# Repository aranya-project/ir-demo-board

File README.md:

# IR Demo FeatherWing

This is a carrier board for an Adafruit Feather device, designed specifically
for the ESP32-S3 Feather. It breaks out two UARTs into IR transceivers, and SPI
to a microSD slot.

## Board View

## Assembly Options

There are three sets of components for the IR transceivers, but only two
can be used. The sections marked IR1 are shared, connected to UART1, and
only one section needs to be populated. The section marked IR2 is
connected to UART2.

Technically, the only components that have to be installed are one
transceiver and two links to power them (across R1/R3 on the top, R2/R4
on the left, and R6/R13 on the right). The capacitors improve stability
but aren't strictly required. The other resistors are pull-ups for the
SD lines (recommended but makes little practical difference) and
pull-ups for the IR shutdown (only really necessary if you plan on
shutting down the CPU)

## IR Transceivers

IR1 is connected to UART1 on the standard Feather TX/RX pins, which are
on GPIOs 39 and 38, respectively. IR2 is connected to UART2 on GPIOs 5
and 6. Each transceiver has an active low enable pin that is by default
pulled high. These are on GPIOs 8 and 9 for IR1 and IR2.

Enabling IrDA mode requires setting `UART_IRDA_EN` in `UART_CONF0_REG`.
Additionally, to transmit, you need to set `UART_IRDA_TX_EN`. By
default, IrDA mode is half duplex, and `UART_IRDA_TX_EN` needs to be
toggled to switch between transmit and receive modes. To enable both
transmit and receive at the same time, which will echo all transmitted
data through the RX line, set `UART_IRDA_DPLX`.

For reasons I don't understand, the only thing that can be set via IDF
APIs is enabling IrDA mode. All of the other IrDA settings are not
available via IDF APIs, so you will likely have to twiddle the registers
directly. In C, this can be done by including `soc/uart_struct.h` and
using the bitfield structs provided. i.e.

```
UART1.conf0.irda_dplx = 1;
```

### Pin Summary (IR1 on UART1)

| GPIO Pin | Function |
|----------|----------|
| 39 | Transmit |
| 38 | Receive |
| 8 | Enable (active low) |

### Pin Summary (IR2 on UART2)

| GPIO Pin | Function |
|----------|----------|
| 5 | Transmit |
| 6 | Receive |
| 9 | Enable (active low) |

## Micro SD

The SD card is connected to SPI such that it should be usable directly
through the IOMUX on IOs 35, 36, and 37. CS is connected to GPIO 11.
Card detect is connected to GPIO 13.

Additionally, DAT1 and DAT2 (only used in SD mode) are connected to
GPIOs 12 and 10, respectively, so you should theoretically be able to
enable 4-bit SD through the SD/MMC controller.

### Pin Summary (SPI mode)

| GPIO Pin | Function |
|----------|----------|
| 36 | SCK |
| 35 | MOSI |
| 37 | MISO |
| 11 | CS |

### Pin Summary (SD 1-bit mode)

| GPIO Pin | Function |
|----------|----------|
| 36 | CLK |
| 35 | CMD |
| 37 | DAT0 |
| 11 | CD |

### Pin Summary (SD 4-bit mode)

| GPIO Pin | Function |
|----------|----------|
| 36 | CLK |
| 35 | CMD |
| 37 | DAT0 |
| 12 | DAT1 |
| 10 | DAT2 |
| 11 | DAT3 |

## Headers

 GPIOs 14-18 are unused and are broken out for futher expansion. The I2C
 lines are also available, as well as VBATT, VBUS, 3V3, GND, EN, and
 ~RST.

## Mechanical

The board is 1.4 inches wide and 2.3 inches tall (35.56 x 58.42mm). The
component sizes should be similar to their footprint outlines, giving it
a maximum horizontal extent of 1.51" (38.354mm) with both side IR
transceivers installed, and a maximum vertical extent of 2.51"
(63.754mm) with the top transceiver installed and an SD card inserted.

Four mounting holes on the corners are sized for M2.5 screws. They are
0.11" (2.794mm) from the edges, which is also the corner radius.

A 0.15x0.25 inch (3.81x6.35mm) cutout is provided near the Feather's
battery connector in the upper right. This allows any battery cables to
be routed below the board even if the board is mounted flush against a
case.

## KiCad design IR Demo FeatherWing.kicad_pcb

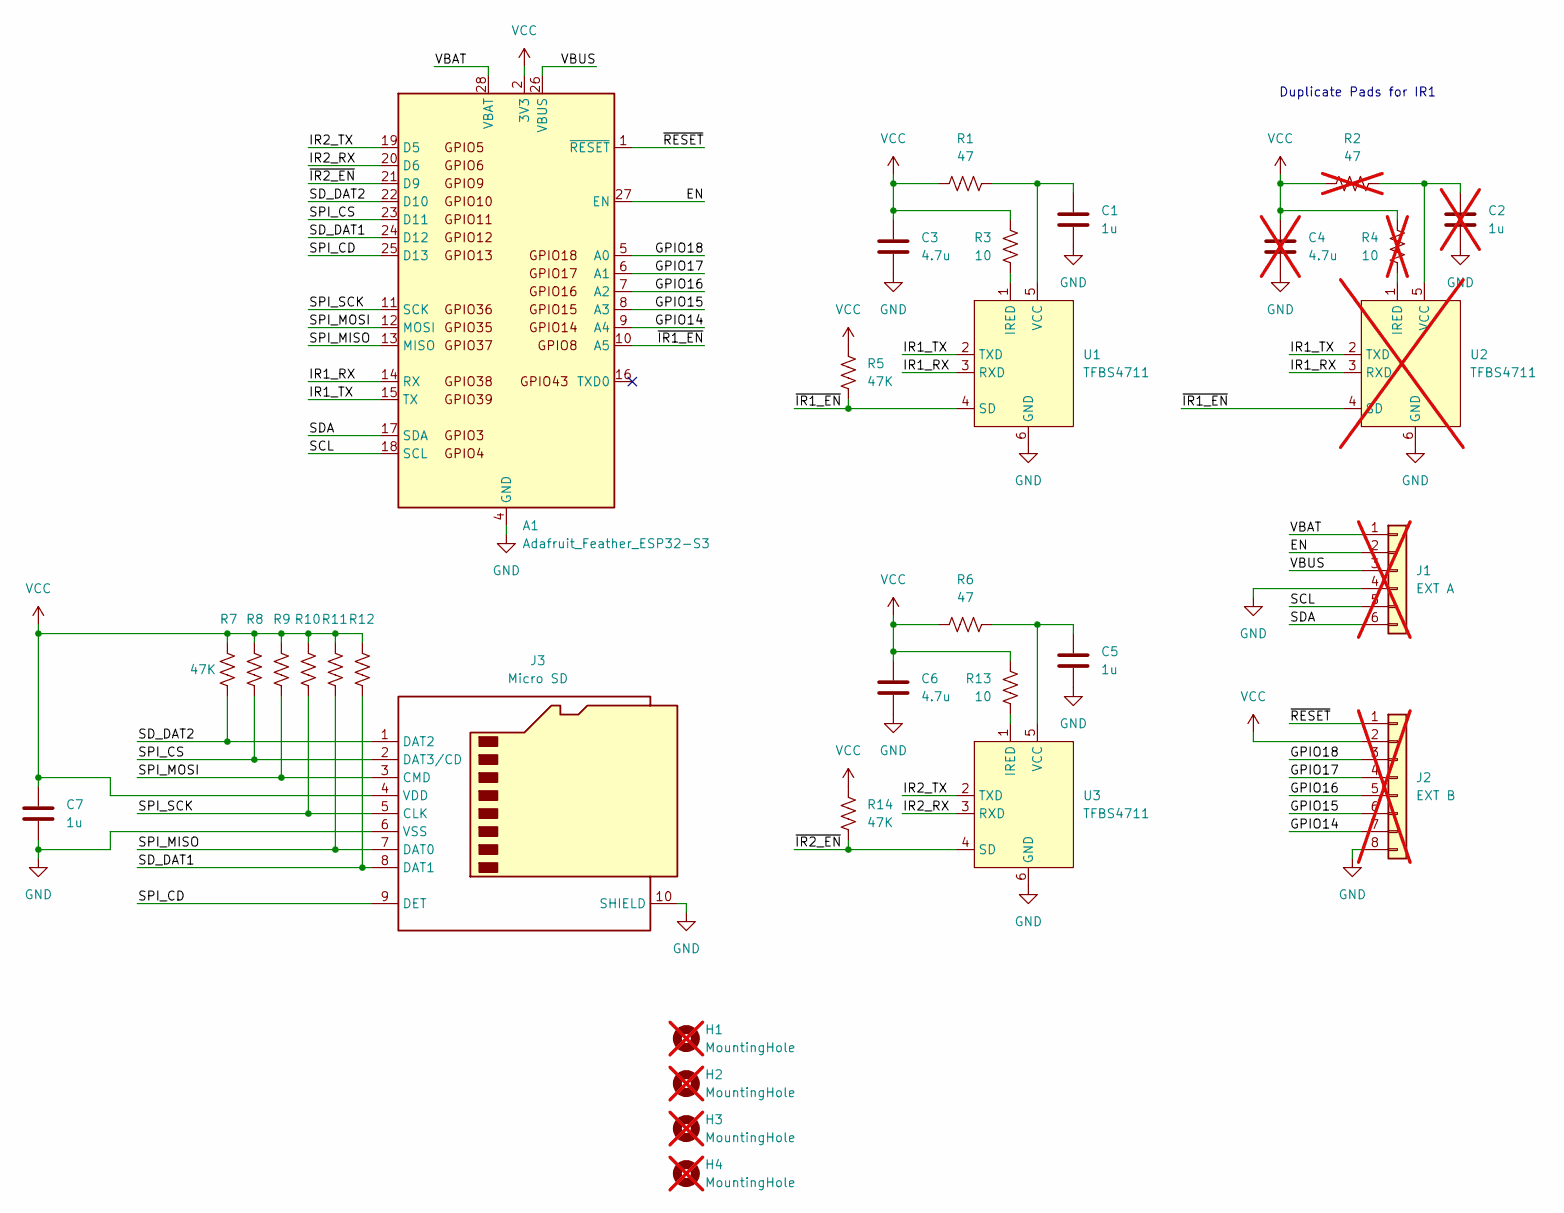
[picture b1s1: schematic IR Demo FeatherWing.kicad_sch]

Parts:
A1: Adafruit_Feather_ESP32-S3; Adafruit_Feather; MPN Adafruit 5477
C1, C5, C7: 1u; C_0805_2012Metric_Pad1.18x1.45mm_HandSolder; MPN C0805C105Z4VACTU
C2: 1u; C_0805_2012Metric_Pad1.18x1.45mm_HandSolder; MPN C0805C105Z4VACTU; not fitted
C3, C6: 4.7u; C_0805_2012Metric_Pad1.18x1.45mm_HandSolder; MPN CL21A475KOFNNNE
C4: 4.7u; C_0805_2012Metric_Pad1.18x1.45mm_HandSolder; MPN CL21A475KOFNNNE; not fitted
H1, H2, H3, H4: MountingHole; MountingHole_2.7mm_M2.5; not fitted
J1: EXT A; PinHeader_1x06_P2.54mm_Vertical; not fitted
J2: EXT B; PinHeader_1x08_P2.54mm_Vertical; not fitted
J3: Micro SD; MSD-4-A; MPN SameSky MSD-4-A
R1, R6: 47; R_0805_2012Metric_Pad1.20x1.40mm_HandSolder; MPN WR08X470 JTL
R2: 47; R_0805_2012Metric_Pad1.20x1.40mm_HandSolder; MPN WR08X470 JTL; not fitted
R3, R13: 10; R_0805_2012Metric_Pad1.20x1.40mm_HandSolder; MPN WR08X100 JTL
R4: 10; R_0805_2012Metric_Pad1.20x1.40mm_HandSolder; MPN WR08X100 JTL; not fitted
R5, R7, R8, R9, R10, R11, R12, R14: 47K; R_0805_2012Metric_Pad1.20x1.40mm_HandSolder; MPN RMCF0805FT47K0
U1, U3: TFBS4711; MPN Vishay TFBS4711
U2: TFBS4711; MPN Vishay TFBS4711; not fitted

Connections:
/EN: A1.27 (EN), J1.2
/GPIO14: A1.9 (A4), J2.7
/GPIO15: A1.8 (A3), J2.6
/GPIO16: A1.7 (A2), J2.5
/GPIO17: A1.6 (A1), J2.4
/GPIO18: A1.5 (A0), J2.3
/IR1_RX: A1.14 (RX), U1.3 (RXD), U2.3 (RXD)
/IR1_TX: A1.15 (TX), U1.2 (TXD), U2.2 (TXD)
/IR2_RX: A1.20 (D6), U3.3 (RXD)
/IR2_TX: A1.19 (D5), U3.2 (TXD)
/SCL: A1.18 (SCL), J1.5
/SDA: A1.17 (SDA), J1.6
/SD_DAT1: A1.24 (D12), J3.8 (DAT1), R12.2
/SD_DAT2: A1.22 (D10), J3.1 (DAT2), R7.2
/SPI_CD: A1.25 (D13), J3.9 (DET)
/SPI_CS: A1.23 (D11), J3.2 (DAT3/CD), R8.2
/SPI_MISO: A1.13 (MISO), J3.7 (DAT0), R11.2
/SPI_MOSI: A1.12 (MOSI), J3.3 (CMD), R9.2
/SPI_SCK: A1.11 (SCK), J3.5 (CLK), R10.2
/VBAT: A1.28 (VBAT), J1.1
/VBUS: A1.26 (VBUS), J1.3
/~IR1_EN: A1.10 (A5), R5.2, U1.4 (SD), U2.4 (SD)
/~IR2_EN: A1.21 (D9), R14.2, U3.4 (SD)
/~RESET: A1.1 (~RESET), J2.1
GND: A1.4 (GND), C1.2, C2.2, C3.2, C4.2, C5.2, C6.2, C7.2, J1.4, J2.8, J3.6 (VSS), J3.10 (SHIELD), U1.6 (GND), U2.6 (GND), U3.6 (GND)
unnamed: R3.2, U1.1 (IRED)
unnamed: C1.1, R1.2, U1.5 (VCC)
unnamed: R4.2, U2.1 (IRED)
unnamed: C2.1, R2.2, U2.5 (VCC)
unnamed: R13.2, U3.1 (IRED)
unnamed: C5.1, R6.2, U3.5 (VCC)
VCC: A1.2 (3V3), A1.3 (3V3), C3.1, C4.1, C6.1, C7.1, J2.2, J3.4 (VDD), R1.1, R2.1, R3.1, R4.1, R5.1, R6.1, R7.1, R8.1, R9.1, R10.1, R11.1, R12.1, R13.1, R14.1

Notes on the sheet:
Duplicate Pads for IR1

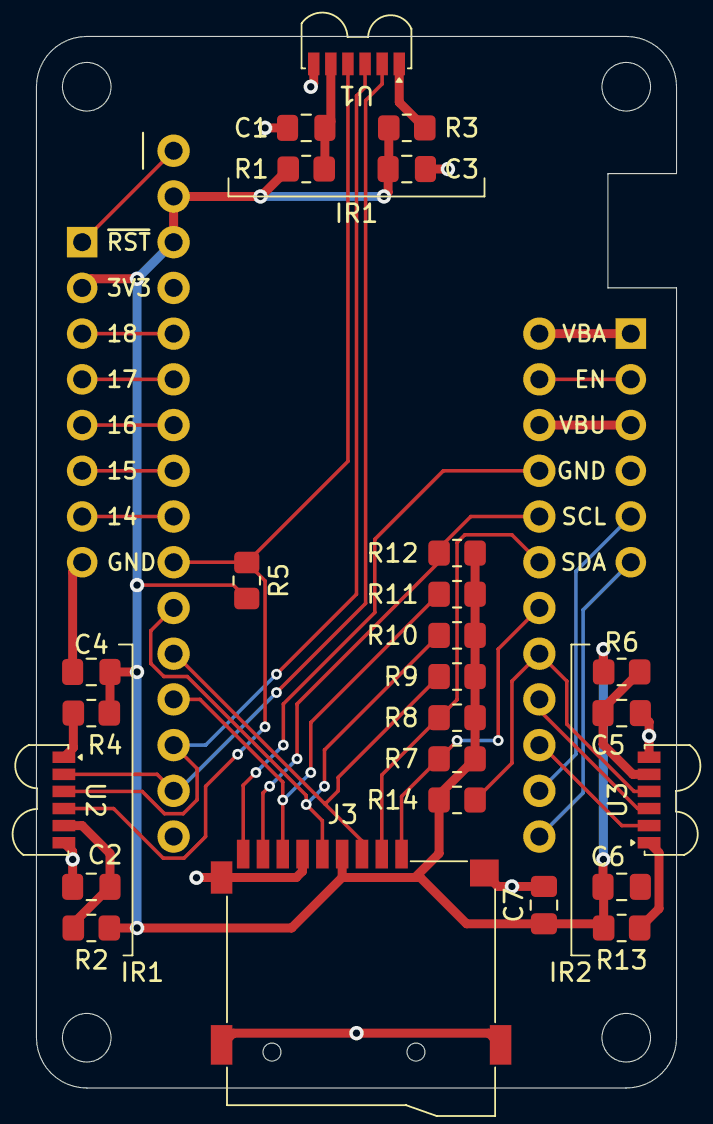
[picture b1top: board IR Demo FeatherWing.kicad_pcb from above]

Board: 2 copper layers, 35.6 x 58.4 mm, 32 parts (0 on the bottom side), 32 nets.

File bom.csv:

"Reference","Value","Footprint","Qty","DNP","MPN"
"A1","Adafruit_Feather_ESP32-S3","Module:Adafruit_Feather","1","","Adafruit 5477"
"C1,C5,C7","1u","Capacitor_SMD:C_0805_2012Metric_Pad1.18x1.45mm_HandSolder","3","","C0805C105Z4VACTU"
"C3,C6","4.7u","Capacitor_SMD:C_0805_2012Metric_Pad1.18x1.45mm_HandSolder","2","","CL21A475KOFNNNE"
"J3","Micro SD","custom8:MSD-4-A","1","","SameSky MSD-4-A"
"R1,R6","47","Resistor_SMD:R_0805_2012Metric_Pad1.20x1.40mm_HandSolder","2","","WR08X470 JTL"
"R3,R13","10","Resistor_SMD:R_0805_2012Metric_Pad1.20x1.40mm_HandSolder","2","","WR08X100 JTL"
"R5,R7,R8,R9,R10,R11,R12,R14","47K","Resistor_SMD:R_0805_2012Metric_Pad1.20x1.40mm_HandSolder","8","","RMCF0805FT47K0"
"U1,U3","TFBS4711","custom8:TFBS4711","2","","Vishay TFBS4711"

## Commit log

2025-02-11 Rev A
2025-02-11 Add BOM and README
2025-02-11 Add gerbers
2025-02-12 Add more dimensions and mechanical description
